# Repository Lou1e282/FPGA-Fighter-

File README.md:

# FPGA Fighter 🎮

> A Street Fighter-inspired 2-player fighting game built on the Nexys 7 FPGA platform using Verilog, VGA display, and state machine-based game logic.

🔗 **Repository**: [github.com/Lou1e282/FPGA-Fighter-](https://github.com/Lou1e282/FPGA-Fighter-.git)

---

## Table of Contents

- [Overview](#overview)
- [Features](#features)
- [Architecture](#architecture)
- [Module Breakdown](#module-breakdown)
- [Implementation Details](#implementation-details)
- [Hardware Requirements](#hardware-requirements)
- [Build & Run](#build--run)
- [Testing & Verification](#testing--verification)
- [Challenges & Solutions](#challenges--solutions)
- [Future Work](#future-work)
- [Author](#author)

---

## Overview

This project implements a real-time 2-player fighting game on an FPGA, rendered through VGA output at 640×480 resolution. Players control characters that can move, jump, and attack, with sprite-based animations driven from BRAM. The game logic is entirely hardware-based, using hierarchical state machines and a centralized game resolver for hit detection and state arbitration.

## Features

- **2-Player Local Multiplayer** — Two players fight in real time with independent controls
- **Sprite Animation System** — Frame-by-frame character animations stored in BRAM (`.mem` format)
- **Hitbox / Hurtbox Combat** — Overlap-based hit detection with configurable attack windows
- **Gravity & Jump Physics** — Hardcoded parabolic jump trajectories with directional air control
- **HP Tracking & Game Over** — Health bars and win/lose conditions with on-screen display
- **External Controller Support** — Custom-built external controller for Player 2
- **VGA 640×480 Output** — Full-screen game rendering with background and UI elements

---

## Architecture

### System Architecture

The architecture separates input handling from game-state resolution. Each player collects their own input signals independently, but their final state is decided by combining those inputs with real-time conditions from the game resolver.

The system filters each player's requested actions through the state priority hierarchy. The game logic evaluates inputs and current conditions, determines and updates the correct states for each player, then drives the VGA display pipeline.

### Player State Machine

In a typical fighting game, state priority follows the hierarchy **HIT > ATTACK > MOVE > IDLE**, and this ordering controls both gameplay logic and animations.

A player can either be **idle** (no inputs), **moving** (changing X/Y position based on controller input), **attacking** (dealing damage to a specific hitbox), or **taking hit** (hurtbox overlapped by opponent's hitbox). These states trigger the corresponding animations and game logic updates.

---

## Module Breakdown

| Module | File | Description |
|---|---|---|
| **Top Design** | `top_twoplayers.v` | Top-level module wiring all submodules, VGA background, debug overlays |
| **Movement** | `player_move.v` | X-axis movement (left/right), jump physics with gravity, position clamping, spawn position |
| **Attack** | `player_attack.v` | Attack signal generation with `attack_active` / `attack_damage` split and pre-attack delay |
| **Game Resolver** | `game_resolver.v` | Hitbox-hurtbox overlap detection, hit event handling, state arbitration |
| **HP Tracker** | `hp_tracker.v` | Health point management per player |
| **VGA Driver** | `vga_640x480.v` | Standard 640×480 VGA timing and signal generation |
| **Sprite Mapper** | `player_sprite_mapper.v` | Maps ROM/BRAM data to sprite frames based on current state and animation frame index |
| **State Animation** | `player_state_anim.v` | Translates player state signals into animation frame sequences |
| **Game Over Text** | `game_over_text.v` | Renders win/lose text overlay |

---

## Implementation Details

### Movement & Jumping (`player_move.v`)

Maps X-position control with button left/right, and jumping with button up. Handling left-right movement and jumping in parallel allows directional jumping. X-position input is locked during each jump, and Y-position changes are hardcoded to mimic gravity for smooth, realistic arcs. Spawn positions after reset are customizable in the top design.

<p align="center">
  <em>X_lock during jumps &nbsp;&nbsp;&nbsp;&nbsp;&nbsp; Hardcoded jump trajectory &nbsp;&nbsp;&nbsp;&nbsp;&nbsp; Position clamp</em>
</p>

### Attack System (`player_attack.v`)

Maps attack action with `btn_down` and generates attack signals for each character. Each attack is handled with two signals:
- **`attack_active`** — triggers attack animations immediately
- **`attack_damage`** — delayed signal (4 + 10 + 4 frame window) that sends real damage to the game resolver

This creates a visible pre-attack windup before damage is applied.

### Game Resolver (`game_resolver.v`)

Inside the game resolver module, hurtboxes and hitboxes are instantiated to send attack events when overlapped during combat. Hit events are handled through private variables inside the resolver to ensure stability.

### VGA Animation System

VGA animation relies on `player_sprite_mapper.v` and `player_state_anim.v`. The sprite mapper reads ROM files containing sprite frames and maps them to corresponding states, while the state animation module gathers state signals and triggers the correct frame sequences.

During implementation, we found that using just ROM to store animations resulted in very long synthesis times. The solution was to store sprite data in **BRAM** through `.mem` format files.

<p align="center">
  <em>Attack animation sprite frames &nbsp;&nbsp;&nbsp;&nbsp;&nbsp;&nbsp;&nbsp;&nbsp;&nbsp;&nbsp; .mem files (44 total)</em>
</p>

All sprites are exactly **126×126 pixels** with 12-bit color depth. The provided VGA 640×480 module serves as the video driver, with backgrounds and debug overlays (hitbox/hurtbox visualization) coded in the top design.

An external controller was also built for Player 2 inputs.

---

## Hardware Requirements

- **FPGA Board**: Nexys 7 (Xilinx Artix-7)
- **Display**: VGA monitor (640×480 @ 60Hz)
- **Input**: On-board buttons (Player 1) + custom external controller (Player 2)
- **Toolchain**: Xilinx Vivado

## Build & Run

1. Clone the repository:
   ```bash
   git clone https://github.com/Lou1e282/FPGA-Fighter-.git
   cd FPGA-Fighter-
   ```

2. Open the project in **Vivado** and add all `.v` source files and `.mem` memory files.

3. Set `top_twoplayers.v` as the top module.

4. Run **Synthesis → Implementation → Generate Bitstream**.

5. Program the Nexys 7 board and connect a VGA monitor.

6. Player 1 uses on-board buttons; Player 2 uses the external controller.

---

## Testing & Verification

Testing was done by individual modules, starting from completing action states of a single player, then scaling to the overall game logic and visual effects.

### 1. Button Input, Move / Attack Test — 11.14

Tested basic player block movement and attacking based on button input.

<p align="center">
  <em>← Jump test &nbsp;&nbsp;&nbsp;&nbsp;&nbsp;&nbsp;&nbsp;&nbsp; Attack test →</em>
</p>

### 2. Character Sprite Mapping Test — 11.20

Integrated character sprite mapper and animation generator to map sprite animation frames to player actions.

<p align="center">
  <em>← Sprite animation &nbsp;&nbsp;&nbsp;&nbsp;&nbsp;&nbsp;&nbsp;&nbsp; Hitbox visualization →</em>
</p>

### 3. Player State Resolver Response Test — 11.28

Full integration test with complete animations, hitstun, and game over conditions.

<p align="center">
  <em>← Complete animation &nbsp;&nbsp;&nbsp;&nbsp;&nbsp;&nbsp;&nbsp;&nbsp; Hitstun →</em>
</p>

### Verification Approach

- **Vivado Simulation**: Used for early debugging of synthesis errors, port mismatches, and state transition issues via waveform analysis
- **On-Board Testing**: Post-implementation verification on VGA monitor with LED indicators mapped to player states

---

## Challenges & Solutions

### BRAM Color Display Errors
Inconsistent sprite dimensions caused color rendering issues. **Fix**: Forced all ROM and `.mem` files to exactly **126×126 pixels**.

### Unresponsive Player Attacks
The attack logic was clocked with the wrong signal. **Fix**: Clocked attacks with the `pixclk` signal that correctly follows button input timing.

### Players Spawning at Wrong Position
Both players spawned at `min_x` instead of `spawn_x`. After investigation, the root cause was found in `player_move` — the reset signal was declared **synchronously**, causing `1'b0` to be fed to the character's X-position on reset, which then got clamped to `min_x`.

<p align="center">
  <em>Assign spawn_x to pos_x &nbsp;&nbsp;&nbsp;&nbsp;&nbsp;&nbsp;&nbsp;&nbsp; Customized instantiation</em>
</p>

**Fix**: Removed rising-edge reset detection and made the reset signal **asynchronous**, completely resolving the issue.

---

## Future Work

- More storage-efficient sprite animations to overcome BRAM limitations
- Multiple attack types and blocking mechanics
- Better input interfacing for richer player states
- Enhanced in-game visual effects (particles, UI polish)
- Stage obstacles and interactive props

---

## Author

**Louie Shen**

*Built for EE 354 — Final Project*

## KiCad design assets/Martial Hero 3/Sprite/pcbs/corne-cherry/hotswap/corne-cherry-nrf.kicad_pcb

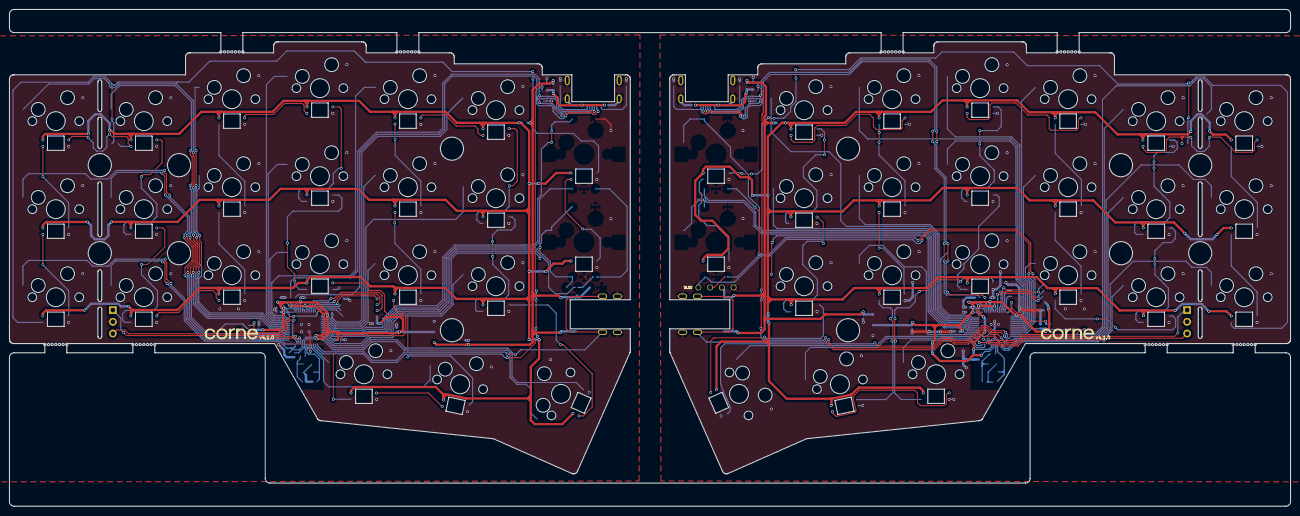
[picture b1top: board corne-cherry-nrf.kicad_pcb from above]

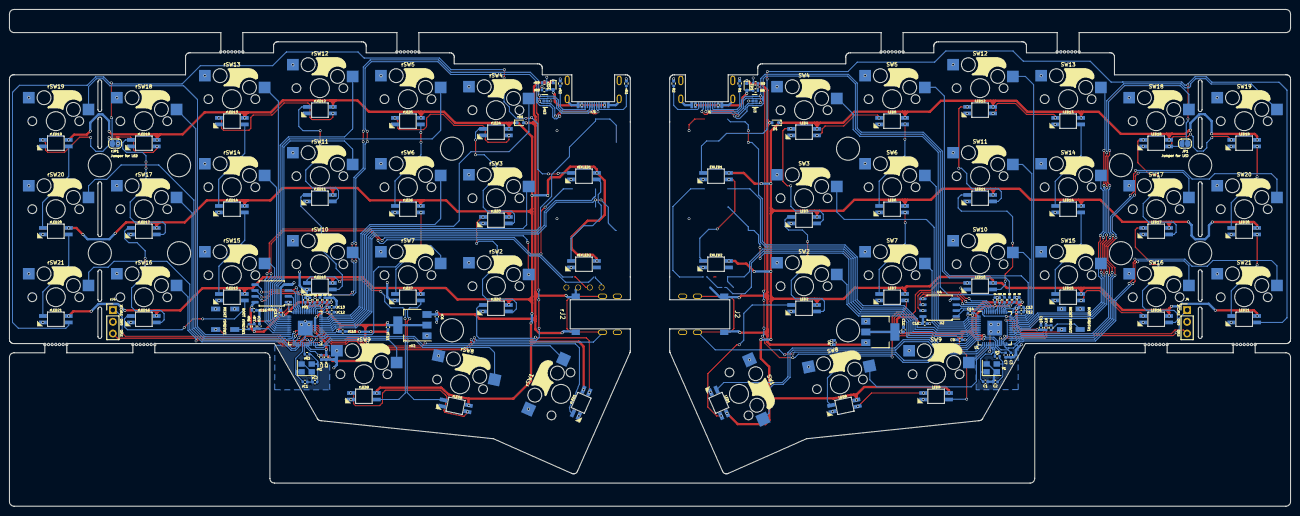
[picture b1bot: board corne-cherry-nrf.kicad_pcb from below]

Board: 2 copper layers, 277.2 x 107.5 mm, 173 parts (164 on the bottom side), 144 nets.

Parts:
BT1, BT2, BT3, BT4: Breakaway Tabs; Breakaway_Tabs
C1, C2: 27p; C_0402_1005Metric
C3, C4, C7, C9, C10, C12, C13, C14, C15: 100n; C_0402_1005Metric
C5, C8, C16: 1u; C_0402_1005Metric
C6, C11: 10u; C_0402_1005Metric
D1: 1N4148WT; D_SOD-523
EXLED1, EXLED2: YS-SK6812MINI-E
J1: TYPE-C-31-M-13C
J2: TRS; PJ-398A-5A_PJ-399B-6A
J4: Conn_01x03; PinHeader_1x03_P2.54mm_Vertical
JP1: SolderJumper_2_Bridged; SolderJumper-2_P1.3mm_Open_RoundedPad1.0x1.5mm
LED1, LED2, LED3, LED4, LED5, LED6, LED7, LED8, LED9, LED10, LED11, LED12, LED13, LED14, LED15, LED16, LED17, LED18, LED19, LED20, LED21: YS-SK6812MINI-E
R1, R2: 5.1k; R_0402_1005Metric
R3, R6: 1k; R_0402_1005Metric
R4, R5: 27; R_0402_1005Metric
R7: 10k; R_0402_1005Metric
R8: 5.6k; R_0402_1005Metric
R9: 10K; R_0402_1005Metric
SMDSW1, SMDSW2: TS-1088R-02026
SW1: SW_Push; keyswitch_cherrymx_hotswap_1.5u
SW2, SW3, SW4, SW5, SW6, SW7, SW8, SW9, SW10, SW11, SW12, SW13, SW14, SW15, SW16, SW17, SW18, SW19, SW20, SW21: SW_Push; keyswitch_cherrymx_hotswap_1u
U1: RP2040; QFN-56-1EP_7x7mm_P0.4mm_EP3.2x3.2mm
U2: NCP1117LPST33T3G; SOT-223-3_TabPin2
U3: TPD4E05U06DQAR; USON-10_2.5x1.0mm_P0.5mm
U4: W25Q128JVSIQ; SOIC-8_5.23x5.23mm_P1.27mm
Y1: 12MHz 18pF; Crystal_SMD_3225-4Pin_3.2x2.5mm
ZD1: RB521S30T1G; D_SOD-523
rBT1, rBT2, rBT3, rBT4: Breakaway Tabs; Breakaway_Tabs
rC1, rC2: 27p; C_0402_1005Metric
rC3, rC4, rC7, rC9, rC10, rC12, rC13, rC14, rC15: 100n; C_0402_1005Metric
rC5, rC8, rC16: 1u; C_0402_1005Metric
rC6, rC11: 10u; C_0402_1005Metric
rD1: 1N4148WT; D_SOD-523
rEXLED1, rEXLED2: YS-SK6812MINI-E
rJ1: TYPE-C-31-M-13C
rJ2: TRS; PJ-398A-5A_PJ-399B-6A
rJ3: Conn_01x04; OLED
rJ4: Conn_01x03; PinHeader_1x03_P2.54mm_Vertical
rJP1: SolderJumper_2_Bridged; SolderJumper-2_P1.3mm_Open_RoundedPad1.0x1.5mm
rLED1, rLED2, rLED3, rLED4, rLED5, rLED6, rLED7, rLED8, rLED9, rLED10, rLED11, rLED12, rLED13, rLED14, rLED15, rLED16, rLED17, rLED18, rLED19, rLED20, rLED21: YS-SK6812MINI-E
rR1, rR2: 5.1k; R_0402_1005Metric
rR3, rR6: 1k; R_0402_1005Metric
rR4, rR5: 27; R_0402_1005Metric
rR7: 10k; R_0402_1005Metric
rR8: 5.6k; R_0402_1005Metric
rR9: 10K; R_0402_1005Metric
rSMDSW1, rSMDSW2: TS-1088R-02026
rSW1: SW_Push; keyswitch_cherrymx_hotswap_1.5u
rSW2, rSW3, rSW4, rSW5, rSW6, rSW7, rSW8, rSW9, rSW10, rSW11, rSW12, rSW13, rSW14, rSW15, rSW16, rSW17, rSW18, rSW19, rSW20, rSW21: SW_Push; keyswitch_cherrymx_hotswap_1u
rU1: RP2040; QFN-56-1EP_7x7mm_P0.4mm_EP3.2x3.2mm
rU2: NCP1117LPST33T3G; SOT-223-3_TabPin2
rU3: TPD4E05U06DQAR; USON-10_2.5x1.0mm_P0.5mm
rU4: W25Q128JVSIQ; SOIC-8_5.23x5.23mm_P1.27mm
rY1: 12MHz 18pF; Crystal_SMD_3225-4Pin_3.2x2.5mm
rZD1: RB521S30T1G; D_SOD-523

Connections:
+1V1: C3.1, C4.1, C5.1, U1.23 (DVDD), U1.45 (VREG_VOUT), U1.50 (DVDD)
+1V1R: rC3.1, rC4.1, rC5.1, rU1.23 (DVDD), rU1.45 (VREG_VOUT), rU1.50 (DVDD)
+3V3: C7.1, C8.1, C9.1, C10.1, C11.1, C12.1, C13.1, C14.1, C15.1, C16.1, R7.2, U1.1 (IOVDD), U1.10 (IOVDD), U1.22 (IOVDD), U1.32 (GPIO21), U1.33 (IOVDD), U1.42 (IOVDD), U1.43 (ADC_AVDD), U1.44 (VREG_IN), U1.48 (USB_VDD), U1.49 (IOVDD), U2.2 (VO), U4.8 (VCC)
+3V3R: rC7.1, rC8.1, rC9.1, rC10.1, rC11.1, rC12.1, rC13.1, rC14.1, rC15.1, rC16.1, rR7.2, rU1.1 (IOVDD), rU1.10 (IOVDD), rU1.22 (IOVDD), rU1.33 (IOVDD), rU1.42 (IOVDD), rU1.43 (ADC_AVDD), rU1.44 (VREG_IN), rU1.48 (USB_VDD), rU1.49 (IOVDD), rU2.2 (VO), rU4.8 (VCC)
+5V: C6.1, D1.2 (A), J2.T, U2.3 (VI), ZD1.1 (K)
+5VR: rC6.1, rD1.2 (A), rJ2.T, rJ3.3, rU2.3 (VI), rZD1.1 (K)
/left/D+: J1.A6 (D+), J1.B6 (D+), R4.1, U3.1 (D1+), U3.4 (D2+), U3.7 (NC), U3.10 (NC)
/left/D-: J1.A7 (D-), J1.B7 (D-), R5.2, U3.2 (D1-), U3.5 (D2-), U3.6 (NC), U3.9 (NC)
/left/KEY1: SW1.1, U1.14 (GPIO11)
/left/KEY2: SW2.1, U1.12 (GPIO9)
/left/KEY3: SW3.1, U1.4 (GPIO2)
/left/KEY4: SW4.1, U1.2 (GPIO0)
/left/KEY5: SW5.1, U1.41 (GPIO29_ADC3)
/left/KEY6: SW6.1, U1.3 (GPIO1)
/left/KEY7: SW7.1, U1.5 (GPIO3)
/left/KEY8: SW8.1, U1.18 (GPIO15)
/left/KEY9: SW9.1, U1.17 (GPIO14)
/left/KEY10: SW10.1, U1.40 (GPIO28_ADC2)
/left/KEY11: SW11.1, U1.39 (GPIO27_ADC1)
/left/KEY12: SW12.1, U1.38 (GPIO26_ADC0)
/left/KEY13: SW13.1, U1.35 (GPIO23)
/left/KEY14: SW14.1, U1.36 (GPIO24)
/left/KEY15: SW15.1, U1.37 (GPIO25)
/left/KEY16: SW16.1, U1.27 (GPIO16)
/left/KEY17: SW17.1, U1.29 (GPIO18)
/left/KEY18: SW18.1, U1.31 (GPIO20)
/left/KEY19: SW19.1, U1.34 (GPIO22)
/left/KEY20: SW20.1, U1.30 (GPIO19)
/left/KEY21: SW21.1, U1.28 (GPIO17)
/left/LED: LED1.4 (DIN), U1.13 (GPIO10)
/left/QSPI_SCLK: U1.52 (QSPI_SCLK), U4.6 (CLK)
/left/QSPI_SD0: U1.53 (QSPI_SD0), U4.5 (DI(IO0))
/left/QSPI_SD1: U1.55 (QSPI_SD1), U4.2 (DO(IO1))
/left/QSPI_SD2: U1.54 (QSPI_SD2), U4.3 (IO2)
/left/QSPI_SD3: U1.51 (QSPI_SD3), U4.7 (IO3)
/left/QSPI_SS: R6.1, R7.1, U1.56 (QSPI_SS), U4.1 (~CS)
/left/SWCLK: J4.1, U1.24 (SWCLK)
/left/SWD: J4.3, U1.25 (SWD)
/left/TX: J2.R, U1.15 (GPIO12)
/left/USB_VBUS_PIN: R8.2, R9.1, U1.16 (GPIO13)
/right/D+: rJ1.A6 (D+), rJ1.B6 (D+), rR4.1, rU3.1 (D1+), rU3.4 (D2+), rU3.7 (NC), rU3.10 (NC)
/right/D-: rJ1.A7 (D-), rJ1.B7 (D-), rR5.2, rU3.2 (D1-), rU3.5 (D2-), rU3.6 (NC), rU3.9 (NC)
/right/KEY1: rSW1.1, rU1.30 (GPIO19)
/right/KEY2: rSW2.1, rU1.34 (GPIO22)
/right/KEY3: rSW3.1, rU1.38 (GPIO26_ADC0)
/right/KEY4: rSW4.1, rU1.39 (GPIO27_ADC1)
/right/KEY5: rSW5.1, rU1.3 (GPIO1)
/right/KEY6: rSW6.1, rU1.40 (GPIO28_ADC2)
/right/KEY7: rSW7.1, rU1.31 (GPIO20)
/right/KEY8: rSW8.1, rU1.28 (GPIO17)
/right/KEY9: rSW9.1, rU1.27 (GPIO16)
/right/KEY10: rSW10.1, rU1.41 (GPIO29_ADC3)
/right/KEY11: rSW11.1, rU1.2 (GPIO0)
/right/KEY12: rSW12.1, rU1.4 (GPIO2)
/right/KEY13: rSW13.1, rU1.5 (GPIO3)
/right/KEY14: rSW14.1, rU1.6 (GPIO4)
/right/KEY15: rSW15.1, rU1.7 (GPIO5)
/right/KEY16: rSW16.1, rU1.29 (GPIO18)
/right/KEY17: rSW17.1, rU1.17 (GPIO14)
/right/KEY18: rSW18.1, rU1.12 (GPIO9)
/right/KEY19: rSW19.1, rU1.11 (GPIO8)
/right/KEY20: rSW20.1, rU1.14 (GPIO11)
/right/KEY21: rSW21.1, rU1.18 (GPIO15)
/right/LED: rLED1.4 (DIN), rU1.13 (GPIO10)
/right/QSPI_SCLK: rU1.52 (QSPI_SCLK), rU4.6 (CLK)
/right/QSPI_SD0: rU1.53 (QSPI_SD0), rU4.5 (DI(IO0))
/right/QSPI_SD1: rU1.55 (QSPI_SD1), rU4.2 (DO(IO1))
/right/QSPI_SD2: rU1.54 (QSPI_SD2), rU4.3 (IO2)
/right/QSPI_SD3: rU1.51 (QSPI_SD3), rU4.7 (IO3)
/right/QSPI_SS: rR6.1, rR7.1, rU1.56 (QSPI_SS), rU4.1 (~CS)
/right/RE1A: rJ3.1, rU1.8 (GPIO6)
/right/REB: rJ3.2, rU1.9 (GPIO7)
/right/SWCLK: rJ4.1, rU1.24 (SWCLK)
/right/SWD: rJ4.3, rU1.25 (SWD)
/right/TX: rJ2.R, rU1.15 (GPIO12)
/right/USB_VBUS_PIN: rR8.2, rR9.1, rU1.16 (GPIO13)
GND: C1.2, C2.2, C3.2, C4.2, C5.2, C6.2, C7.2, C8.2, C9.2, C10.2, C11.2, C12.2, C13.2, C14.2, C15.2, C16.2, EXLED1.3 (VSS), EXLED2.3 (VSS), J1.A1 (GND), J1.A12 (GND), J1.B1 (GND), J1.B12 (GND), J1.S1 (SHIELD), J2.S, J4.2, LED1.3 (VSS), LED2.3 (VSS), LED3.3 (VSS), LED4.3 (VSS), LED5.3 (VSS), LED6.3 (VSS), LED7.3 (VSS), LED8.3 (VSS), LED9.3 (VSS), LED10.3 (VSS), LED11.3 (VSS), LED12.3 (VSS), LED13.3 (VSS), LED14.3 (VSS), LED15.3 (VSS), LED16.3 (VSS), LED17.3 (VSS), LED18.3 (VSS), LED19.3 (VSS), LED20.3 (VSS), LED21.3 (VSS), R1.1, R2.1, R9.2, SMDSW1.1, SMDSW2.1, SW1.2, SW2.2, SW3.2, SW4.2, SW5.2, SW6.2, SW7.2, SW8.2, SW9.2, SW10.2, SW11.2, SW12.2, SW13.2, SW14.2, SW15.2, SW16.2, SW17.2, SW18.2, SW19.2, SW20.2, SW21.2, U1.19 (TESTEN), U1.57 (GND), U2.1 (GND), U3.3 (GND), U3.8 (GND), U4.4 (GND), Y1.2, Y1.4
GNDR: rC1.2, rC2.2, rC3.2, rC4.2, rC5.2, rC6.2, rC7.2, rC8.2, rC9.2, rC10.2, rC11.2, rC12.2, rC13.2, rC14.2, rC15.2, rC16.2, rEXLED1.3 (VSS), rEXLED2.3 (VSS), rJ1.A1 (GND), rJ1.A12 (GND), rJ1.B1 (GND), rJ1.B12 (GND), rJ1.S1 (SHIELD), rJ2.S, rJ3.4, rJ4.2, rLED1.3 (VSS), rLED2.3 (VSS), rLED3.3 (VSS), rLED4.3 (VSS), rLED5.3 (VSS), rLED6.3 (VSS), rLED7.3 (VSS), rLED8.3 (VSS), rLED9.3 (VSS), rLED10.3 (VSS), rLED11.3 (VSS), rLED12.3 (VSS), rLED13.3 (VSS), rLED14.3 (VSS), rLED15.3 (VSS), rLED16.3 (VSS), rLED17.3 (VSS), rLED18.3 (VSS), rLED19.3 (VSS), rLED20.3 (VSS), rLED21.3 (VSS), rR1.1, rR2.1, rR9.2, rSMDSW1.1, rSMDSW2.1, rSW1.2, rSW2.2, rSW3.2, rSW4.2, rSW5.2, rSW6.2, rSW7.2, rSW8.2, rSW9.2, rSW10.2, rSW11.2, rSW12.2, rSW13.2, rSW14.2, rSW15.2, rSW16.2, rSW17.2, rSW18.2, rSW19.2, rSW20.2, rSW21.2, rU1.19 (TESTEN), rU1.32 (GPIO21), rU1.57 (GND), rU2.1 (GND), rU3.3 (GND), rU3.8 (GND), rU4.4 (GND), rY1.2, rY1.4
unnamed: C2.1, R3.1, Y1.3
unnamed: D1.1 (K), EXLED1.1 (VDD), EXLED2.1 (VDD), LED1.1 (VDD), LED2.1 (VDD), LED3.1 (VDD), LED4.1 (VDD), LED5.1 (VDD), LED6.1 (VDD), LED7.1 (VDD), LED8.1 (VDD), LED9.1 (VDD), LED10.1 (VDD), LED11.1 (VDD), LED12.1 (VDD), LED13.1 (VDD), LED14.1 (VDD), LED15.1 (VDD), LED16.1 (VDD), LED17.1 (VDD), LED18.1 (VDD), LED19.1 (VDD), LED20.1 (VDD), LED21.1 (VDD)
unnamed: EXLED1.4 (DIN), JP1.2 (B), LED21.2 (DOUT)
unnamed: EXLED1.2 (DOUT), EXLED2.4 (DIN)
unnamed: J1.A5 (CC1), R1.2
unnamed: J1.B5 (CC2), R2.2
unnamed: JP1.1 (A), LED18.2 (DOUT), LED19.4 (DIN)
unnamed: LED1.2 (DOUT), LED2.4 (DIN)
unnamed: LED2.2 (DOUT), LED3.4 (DIN)
unnamed: LED3.2 (DOUT), LED4.4 (DIN)
unnamed: LED4.2 (DOUT), LED5.4 (DIN)
unnamed: LED5.2 (DOUT), LED6.4 (DIN)
unnamed: LED6.2 (DOUT), LED7.4 (DIN)
unnamed: LED7.2 (DOUT), LED8.4 (DIN)
unnamed: LED8.2 (DOUT), LED9.4 (DIN)
unnamed: LED9.2 (DOUT), LED10.4 (DIN)
unnamed: LED10.2 (DOUT), LED11.4 (DIN)
unnamed: LED11.2 (DOUT), LED12.4 (DIN)
unnamed: LED12.2 (DOUT), LED13.4 (DIN)
unnamed: LED13.2 (DOUT), LED14.4 (DIN)
unnamed: LED14.2 (DOUT), LED15.4 (DIN)
unnamed: LED15.2 (DOUT), LED16.4 (DIN)
unnamed: LED16.2 (DOUT), LED17.4 (DIN)
unnamed: LED17.2 (DOUT), LED18.4 (DIN)
unnamed: LED19.2 (DOUT), LED20.4 (DIN)
unnamed: LED20.2 (DOUT), LED21.4 (DIN)
unnamed: R6.2, SMDSW1.2
unnamed: SMDSW2.2, U1.26 (RUN)
unnamed: R5.1, U1.46 (USB_DM)
unnamed: R4.2, U1.47 (USB_DP)
unnamed: C1.1, U1.20 (XIN), Y1.1
unnamed: R3.2, U1.21 (XOUT)
unnamed: rC2.1, rR3.1, rY1.3
unnamed: rD1.1 (K), rEXLED1.1 (VDD), rEXLED2.1 (VDD), rLED1.1 (VDD), rLED2.1 (VDD), rLED3.1 (VDD), rLED4.1 (VDD), rLED5.1 (VDD), rLED6.1 (VDD), rLED7.1 (VDD), rLED8.1 (VDD), rLED9.1 (VDD), rLED10.1 (VDD), rLED11.1 (VDD), rLED12.1 (VDD), rLED13.1 (VDD), rLED14.1 (VDD), rLED15.1 (VDD), rLED16.1 (VDD), rLED17.1 (VDD), rLED18.1 (VDD), rLED19.1 (VDD), rLED20.1 (VDD), rLED21.1 (VDD)
unnamed: rEXLED1.4 (DIN), rJP1.2 (B), rLED21.2 (DOUT)
unnamed: rEXLED1.2 (DOUT), rEXLED2.4 (DIN)
unnamed: rJ1.A5 (CC1), rR1.2
unnamed: rJ1.B5 (CC2), rR2.2
unnamed: rJP1.1 (A), rLED18.2 (DOUT), rLED19.4 (DIN)
unnamed: rLED1.2 (DOUT), rLED2.4 (DIN)
unnamed: rLED2.2 (DOUT), rLED3.4 (DIN)
unnamed: rLED3.2 (DOUT), rLED4.4 (DIN)
unnamed: rLED4.2 (DOUT), rLED5.4 (DIN)
unnamed: rLED5.2 (DOUT), rLED6.4 (DIN)
unnamed: rLED6.2 (DOUT), rLED7.4 (DIN)
unnamed: rLED7.2 (DOUT), rLED8.4 (DIN)
unnamed: rLED8.2 (DOUT), rLED9.4 (DIN)
unnamed: rLED9.2 (DOUT), rLED10.4 (DIN)
unnamed: rLED10.2 (DOUT), rLED11.4 (DIN)
unnamed: rLED11.2 (DOUT), rLED12.4 (DIN)
unnamed: rLED12.2 (DOUT), rLED13.4 (DIN)
unnamed: rLED13.2 (DOUT), rLED14.4 (DIN)
unnamed: rLED14.2 (DOUT), rLED15.4 (DIN)
unnamed: rLED15.2 (DOUT), rLED16.4 (DIN)
unnamed: rLED16.2 (DOUT), rLED17.4 (DIN)
unnamed: rLED17.2 (DOUT), rLED18.4 (DIN)
unnamed: rLED19.2 (DOUT), rLED20.4 (DIN)
unnamed: rLED20.2 (DOUT), rLED21.4 (DIN)
unnamed: rR6.2, rSMDSW1.2
unnamed: rSMDSW2.2, rU1.26 (RUN)
unnamed: rR5.1, rU1.46 (USB_DM)
unnamed: rR4.2, rU1.47 (USB_DP)
unnamed: rC1.1, rU1.20 (XIN), rY1.1
unnamed: rR3.2, rU1.21 (XOUT)
VBUS: J1.A4 (VBUS), J1.A9 (VBUS), J1.B4 (VBUS), J1.B9 (VBUS), R8.1, ZD1.2 (A)
VBUSR: rJ1.A4 (VBUS), rJ1.A9 (VBUS), rJ1.B4 (VBUS), rJ1.B9 (VBUS), rR8.1, rZD1.2 (A)

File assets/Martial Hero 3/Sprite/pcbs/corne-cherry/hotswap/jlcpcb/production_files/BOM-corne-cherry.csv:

Comment,Designator,Footprint,LCSC
W25Q128JVSIQ,"U4,rU4",SOIC-8_5.23x5.23mm_P1.27mm,C113767
1k,"R3,R6,rR3,rR6",R_0402_1005Metric,C11702
TRS,"J2,rJ2",PJ-398A-5A_PJ-399B-6A,C128994
TPD4E05U06DQAR,"U3,rU3",USON-10_2.5x1.0mm_P0.5mm,C138714
RB521S30T1G,"ZD1,rZD1",D_SOD-523,C145179
NCP1117LPST33T3G,"U2,rU2",SOT-223-3_TabPin2,C146799
100n,"C10,C12,C13,C14,C15,C3,C4,C7,C9,rC10,rC12,rC13,rC14,rC15,rC3,rC4,rC7,rC9",C_0402_1005Metric,C1525
10u,"C11,C6,rC11,rC6",C_0402_1005Metric,C15525
27p,"C1,C2,rC1,rC2",C_0402_1005Metric,C1557
RP2040,"U1,rU1",QFN-56-1EP_7x7mm_P0.4mm_EP3.2x3.2mm,C2040
1N4148WT,"D1,rD1",D_SOD-523,C232841
10k,"R7,R9,rR7,rR9",R_0402_1005Metric,C25744
5.1k,"R1,R2,rR1,rR2",R_0402_1005Metric,C25905
5.6k,"R8,rR8",R_0402_1005Metric,C25908
TYPE-C-31-M-13C,"J1,rJ1",TYPE-C-31-M-13C,C2848620
27,"R4,R5,rR4,rR5",R_0402_1005Metric,C2909343
TS-1088R-02026,"SMDSW1,SMDSW2,rSMDSW1,rSMDSW2",TS-1088R-02026,C455280
YS-SK6812MINI-E,"EXLED1,EXLED2,LED1,LED10,LED11,LED12,LED13,LED14,LED15,LED16,LED17,LED18,LED19,LED2,LED20,LED21,LED3,LED4,LED5,LED6,LED7,LED8,LED9,rEXLED1,rEXLED2,rLED1,rLED10,rLED11,rLED12,rLED13,rLED14,rLED15,rLED16,rLED17,rLED18,rLED19,rLED2,rLED20,rLED21,rLED3,rLED4,rLED5,rLED6,rLED7,rLED8,rLED9",YS-SK6812MINI-E,C5149201
RotaryEncoder_Switch,"EXSW1,EXSW2,SW1,SW10,SW11,SW12,SW13,SW14,SW15,SW16,SW17,SW18,SW19,SW2,SW20,SW21,SW3,SW4,SW5,SW6,SW7,SW8,SW9,rEXSW1,rEXSW2,rSW1,rSW10,rSW11,rSW12,rSW13,rSW14,rSW15,rSW16,rSW17,rSW18,rSW19,rSW2,rSW20,rSW21,rSW3,rSW4,rSW5,rSW6,rSW7,rSW8,rSW9",keyswitch_cherrymx_hotswap_1u_rotary_encoder_ec12,C5156480
1u,"C16,C5,C8,rC16,rC5,rC8",C_0402_1005Metric,C52923
12MHz 18pF,"Y1,rY1",Crystal_SMD_3225-4Pin_3.2x2.5mm,C91749

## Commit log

2025-11-09 initialcommit
2025-11-09 player
2025-11-09 player_move
2025-11-09 arch?
2025-11-12 move attack
2025-11-12 game arch
2025-11-14 added test without sprites and temp top module
2025-11-14 proposal
2025-11-14 player_move_test
2025-11-14 atleastitcompiles
2025-11-14 movetest
2025-11-15 movetestfixed
2025-11-15 movetestfixed2
2025-11-16 1bt attacktest1
2025-11-16 1pl attack test done
2025-11-17 player_state_amin
2025-11-18 spritetestdone
2025-11-19 BRAM tested
2025-11-20 moveattacktest
2025-11-20 pvp test
2025-11-21 1playertest
2025-11-22 player_move mod fix
2025-11-23 p1p2fix
2025-11-30 attackanimationfix
2025-12-01 game resolver
2025-12-02 hpfi
2025-12-03 hpbar and attack
2025-12-03 core test done
2025-12-03 spawn fix?
2025-12-04 p2 test
2025-12-04 2nd controller
2025-12-17 final
2026-03-13 cleaned files, added readme.md
